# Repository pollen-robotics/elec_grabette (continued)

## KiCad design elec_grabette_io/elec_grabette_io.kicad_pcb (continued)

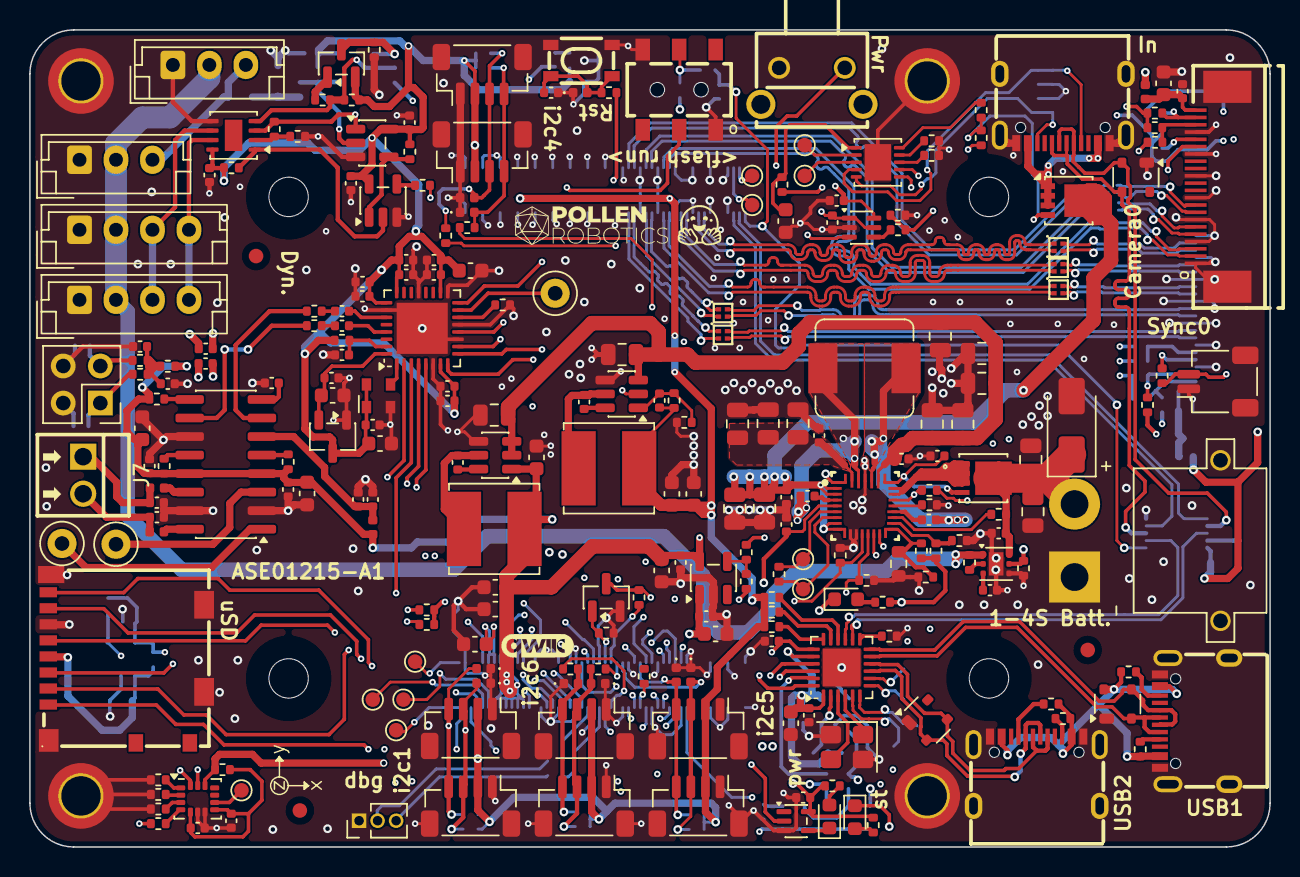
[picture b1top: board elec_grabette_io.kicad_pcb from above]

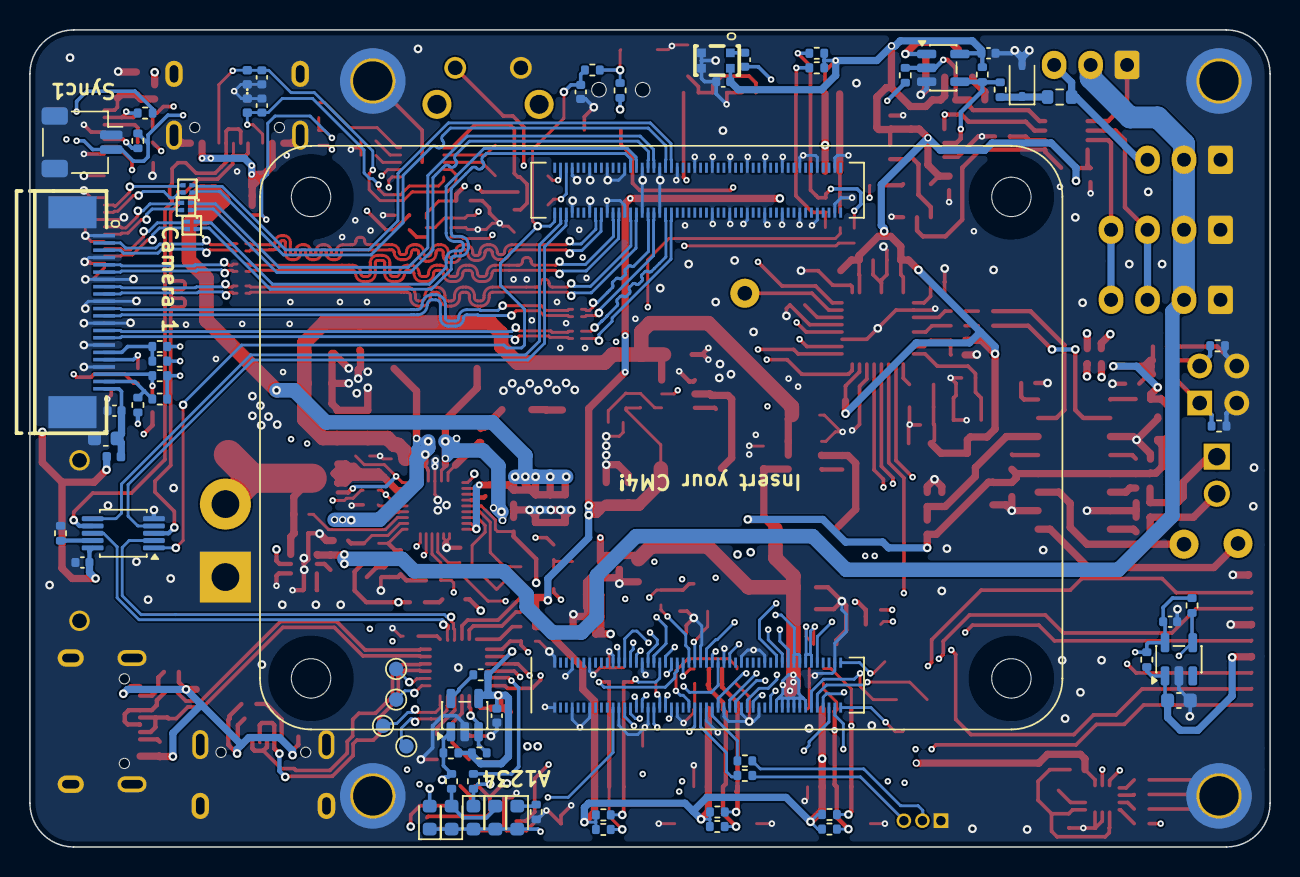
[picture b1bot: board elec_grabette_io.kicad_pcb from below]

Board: 4 copper layers, 85.0 x 56.0 mm, 324 parts (72 on the bottom side), 231 nets.

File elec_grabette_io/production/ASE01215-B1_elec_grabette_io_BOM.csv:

Designator,Footprint,Quantity,Value,LCSC Part #
"C1, C15, C16, C17, C18, C19, C2, C20, C37, C4, C5, C6, C7, C70, C72, C74, C76, C77, C78, C80, C82, C85, C87, C92, C93",0402,25,100n,C307331
"C10, C11, C12, C13, C21, C22, C23, C24, C26, C27, C28, C3, C30, C31, C32, C35, C79",0402,17,1u,C52923
"C14, C29, C33, C67, C69, C73, C75, C8, C81, C83, C86, C9",0603,12,10u,C1691
C25,0402,1,10n,C15195
"C34, C36",0402,2,220p,C71693
"C38, C39",0402,2,100n 6V3,C1525
"C40, C41",0402,2,330p 35V,C106206
C42,0603,1,1u 35V,C15849
"C43, C45, C52, C53, C54, C55, C56, C57, C58, C59, C60, C61, C62, C63",0805,14,10u 25V,C15850
C44,0402,1,4u7 16V,C23733
"C46, C50, C51, C64, C65",0402,5,100n 50V,C307331
"C47, C48",0402,2,47n,C880605
C49,0402,1,DNP - 1n 50V,
"C66, C68, C71, C90, C91",0603,5,22u 6V3,C84419
C84,0402,1,DNP-100n,
C88,0402,1,100p,C106200
D1,D_SOD-323,1,5V1,C151348
"D10, D21, D22, D23, D24, D25, D26, D27, D28, D29, D30",0402,11,5V bidir ESD Diode,C48260
"D11, D12, D8",0603,3,Green,C19171301
"D13, D14, D15, D16, D17",0603,5,LED_Small,C7429915
"D18, D19, D20",SOT-143,3,SP0503BAHT,C3040626
D9,D_SMA,1,SMAJ8.0A,C1972936
FB1,0402,1,1.3A 600R@100MHz,C76884
"FB2, FB3, FB4, FB5",0402,4,2A - 120R@100MHz,C88970
"J1, J2",JST_EH_B4B-EH-A_1x04_P2.50mm_Vertical,2,Dynamixel-4,C160258
"J10, J11, J19, J20, J21, J22, J8, J9",JST_SH_BM04B-SRSS-TB_1x04-1MP_P1.00mm_Vertical,8,JST SH,C51940129
J12,AMASS_XT30PW-M_1x02_P2.50mm_Horizontal,1,XT30,C431092
J13,PinHeader_1x03_P1.27mm_Vertical,1,DNP-Header 1x3,P125-1103A1BS116A
"J14, J15",FPC-SMD_AFC07-S22ECA-00,2,FPC Camera,C262642
"J16, J17, J18",USB-C-SMD_TYPE-C-6PIN-2MD-073 Shou Han - C2765186,3,USB-C,C2765186
J23,PinHeader_2x02_P2.54mm_Vertical,1,"Header 2,54 2x2",
J24,SIM-SMD_8P-1040310811,1,Micro_SD_Card_Det2,C585350
"J25, J26",position_only,2,CM4 Connector,C597931
"J27, J28",JST_SH_SM02B-SRSS-TB_1x02-1MP_P1.00mm_Horizontal,2,JST SH,C160402
"J3, J4",JST_EH_B3B-EH-A_1x03_P2.50mm_Vertical,2,Dynamixel-3,C160259
J7,CONN-TH_DB125-2.54-2P-GN,1,Screw term.,C918120
L1,L_Sumida_CDMC6D28_7.25x6.5mm,1,1uH-10A,C87572
"L10, L11, L4, L5, L6, L7, L8, L9",FILTER-SMD_4P-L0.8-W0.6-TL_DLP0NSC280HL2L,8,DLM0NSN500HY2D,C913480
"L2, L3",L_Bourns_SRN6045TA,2,"6,8u 2A",C57254
MK1,MIC-SMD_4P-L2.8-W1.9-P1.84-TL,1,Microphone_MEMS,C7587901
Q1,SOT-23,1,MMBT3906,C727128
Q2,Vishay_PowerPAK_1212-8_Single,1,SiS443DN,C41355039
Q3,SOT-23,1,BSS123,C7420338
Q4,PQFN_3.3x3.3mm_-_PG-TDSON-8_FL,1,CSD17575Q3,C529277
"R1, R11, R13, R14, R2, R26, R27, R28, R30, R31, R32, R4, R41, R42, R49, R6, R79, R81, R84, R9, R98",0402,21,10k,C25744
"R10, R8",0402,2,150R,C2909321
"R100, R64",0402,2,DNP-0R,RC0402JR-070RL
"R101, R102, R71, R77",0402,4,DNP-0R,C17168
"R103, R12, R15, R16, R17, R23, R24, R33, R34, R35, R36, R37, R5, R56, R57, R58, R59, R60, R61, R63, R65, R66, R67, R70, R80, R82, R83, R85, R93, R99",0402,30,0R,C17168
"R104, R39, R44, R48, R55, R78",0402,6,100k,C22369186
R105,0402,1,62k,C137950
"R18, R46",0402,2,1k,C105637
"R19, R20",0402,2,4k7,C105871
"R21, R22",0402,2,DNP-1M,
"R25, R29, R88",0402,3,DNP-10k,
R3,0402,1,20k,C25765
R38,0402,1,10R,C138066
R40,0402,1,22k6,C100316
R43,0402,1,220k,C138030
"R45, R47, R7",0402,3,DNP-0R,
R50,0402,1,6k04,C97819
R51,0402,1,100R,C106232
R52,0402,1,5k23,C2933105
R53,0402,1,30k1,C2998131
R54,0402,1,127k,C5126094
R62,0402,1,220R,C112291
"R68, R69, R87, R89",0402,4,5k1,C25905
"R72, R73",0402,2,2k2,C2906865
"R74, R75",0402,2,DNP-2k2,
R76,0402,1,196k,C852585
R86,0402,1,2k7,C138017
"R90, R91, R92",0402,3,330R,C2906929
"R94, R95, R96, R97",0402,4,56k,C114756
SW1,KEY-TH_TC-6615-7-160G,1,SW_Push,C2845275
SW2,KEY-SMD_4P-L4.2-W3.2-P2.20-LS4.6,1,Tactile Switch,C127488
SW3,SW-SMD_6P-L7.2-W3.5-P2.50-LS6.0-TL,1,SW_DPDT,C2837066
TH1,0603,1,100R thermistor,C913703
TH2,0603,1,10k_NTC,C554013
U1,SOT-23-5,1,74LVC1G08,C7666
U10,WDFN-10-1EP_3x3mm_P0.5mm_EP1.8x2.5mm,1,HUSB238_002DD,C7471904
U11,RQM0029A-MFG,1,BQ25792RQMR,C2862876
U12,TSOT-23-6,1,AP63205,C2071056
U13,TSOT-23-6,1,AP63201,C2071044
U15,SOT-353_SC-70-5,1,SN74LVC1G07DCK,C55509819
U16,MSOP-10_3x3mm_P0.5mm,1,SGM7222YMS10/TR,C113292
U17,WQFN-24-1EP_4x4mm_P0.5mm_EP2.6x2.6mm,1,FE1.1s,C6776948
U18,SOT-23-5,1,DNP-24C02S,
U19,SOT-23-5,1,TPS2041B,C51386
U2,SOT-23-5,1,SN74LVC1G125DBV,C23654
U20,TSOT-23-5,1,RT9742GGJ5,C250547
U21,SOT-363_SC-70-6,1,SN74LVC1T45DCK,C9382
U3,SOT-23-5,1,SN74LVC1G126DBVR,C7834
U4,WSON-6-1EP_2x2mm_P0.65mm_EP1x1.6mm,1,tp,C527679
U5,DFN-8-1EP_3x3mm_P0.65mm_EP1.2x2.15mm,1,GM3088ENA,C49423279
U6,SOT-23-3,1,XC6206P182MR,C347373
U7,VQFN-32-1EP_5x5mm_P0.5mm_EP3.5x3.5mm,1,TLV320AIC3104IRHBR,C181753
U8,SOIC-16_3.9x9.9mm_P1.27mm,1,PAM8406D,C86270
U9,LGA-14_3x2.5mm_P0.5mm_LayoutBorder3x4y,1,LSM6DSV16XTR,C5267406
Y1,Oscillator_SMD_Abracon_ASDMB-4Pin_2.5x2.0mm,1,12 MHz,C7425459
Y2,Crystal_SMD_3225-4Pin_3.2x2.5mm,1,12MHz,C133334
